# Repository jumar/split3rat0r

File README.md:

# d3vastat0r
My first 60 key ortholinear keyboard with top mounted components. 
This keyboard is inspired by the Plaid keyboard, but much simpler since I don't know enough to use all those components the Plaid uses.

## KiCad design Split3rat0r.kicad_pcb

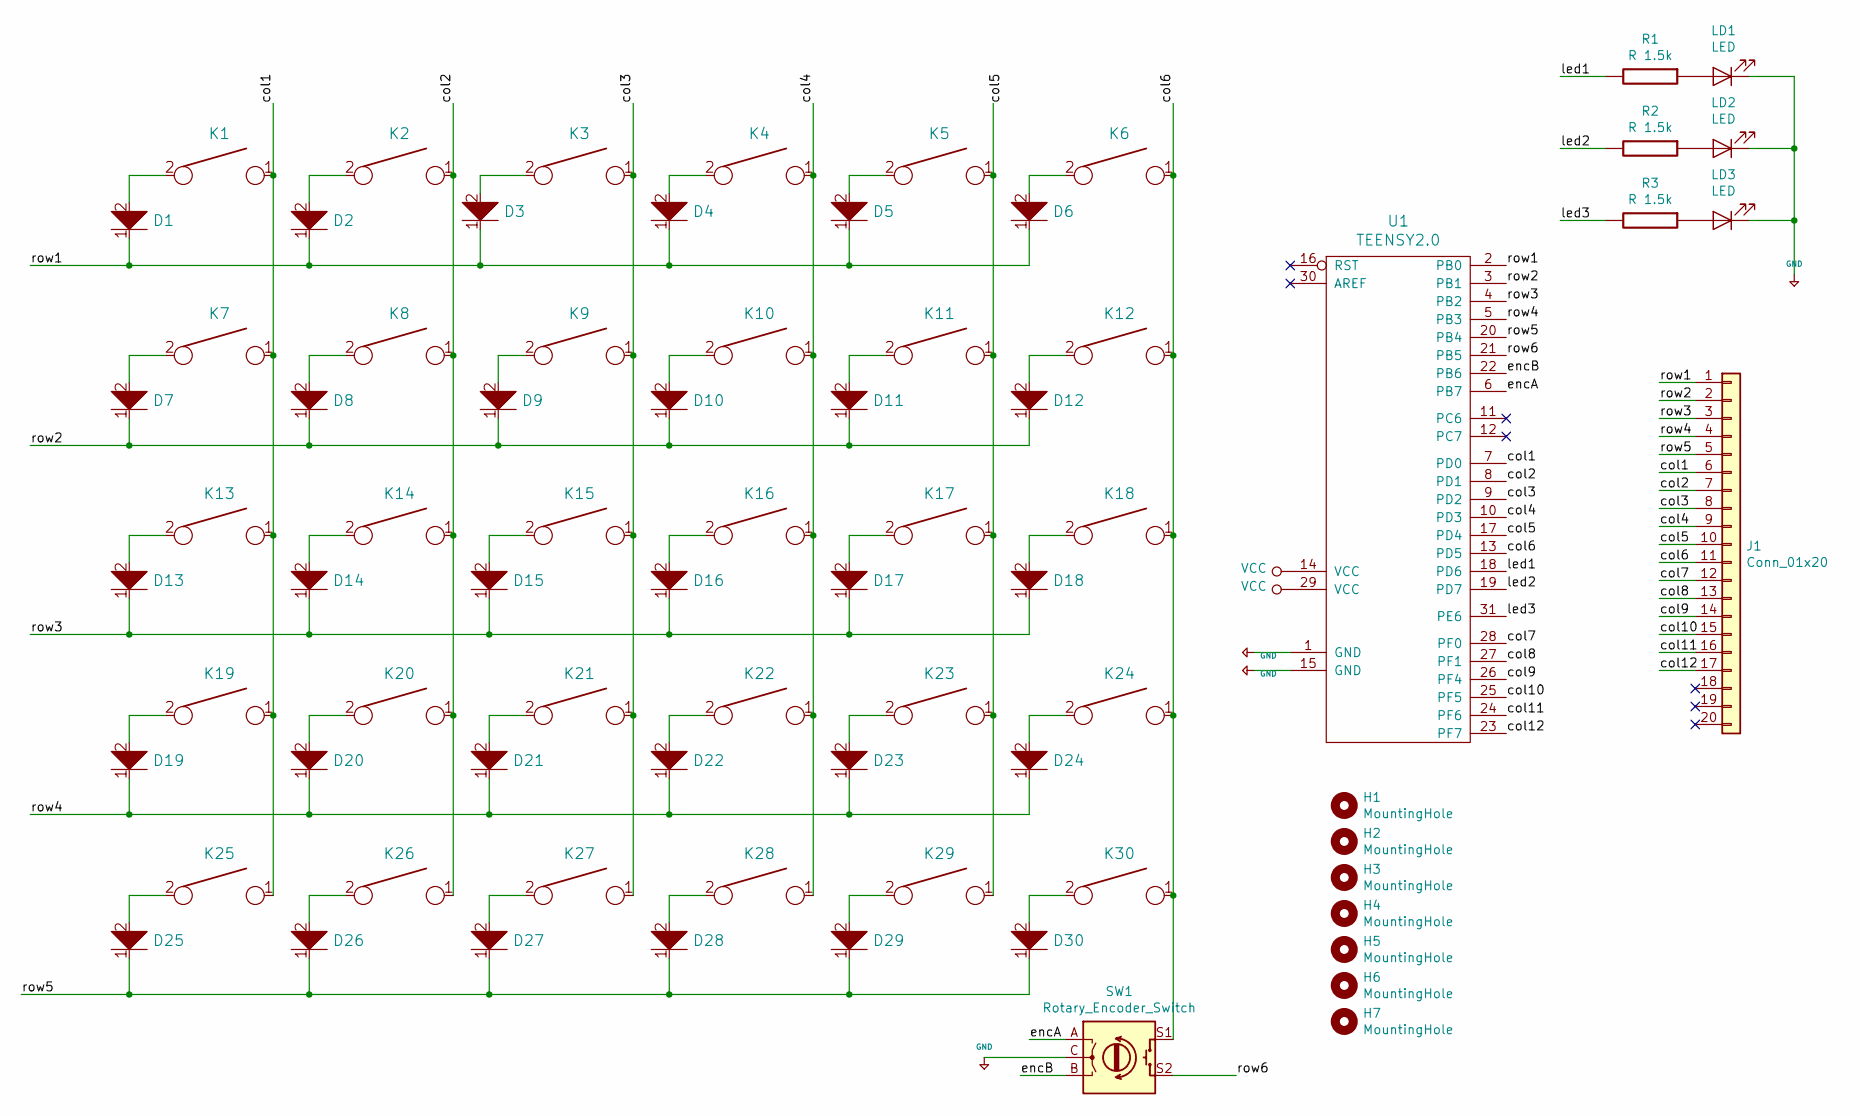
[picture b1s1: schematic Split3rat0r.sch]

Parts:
D1, D2, D3, D4, D5, D6, D7, D8, D9, D10, D11, D12, D13, D14, D15, D16, D17, D18, D19, D20, D21, D22, D23, D24, D25, D26, D27, D28, D29, D30: D; D_axial
H1, H2, H3, H4, H5, H6, H7: MountingHole; MountingHole_2.2mm_M2_Pad
J1: Conn_01x20; IDC-Header_2x10_P2.54mm_Horizontal
K1, K2, K3, K4, K5, K6, K7, K8, K9, K10, K11, K12, K13, K14, K15, K16, K17, K18, K19, K20, K21, K22, K23, K24, K25, K26, K27, K28, K29, K30: KEYSW; SW_Cherry_MX_1.00u_PCB
LD1, LD2, LD3: LED; LED_TH
R1, R2, R3: R 1.5k; R_Axial_DIN0204_L3.6mm_D1.6mm_P5.08mm_Horizontal
SW1: Rotary_Encoder_Switch; RotaryEncoder_Alps_EC11E-Switch_Vertical_H20mm
U1: TEENSY2.0; Teensy_20

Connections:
+5V: LD1.1 (K), LD2.1 (K), LD3.1 (K), SW1.C, U1.1 (GND), U1.15 (GND)
/col1: J1.6, K1.1, K7.1, K13.1, K19.1, K25.1, U1.7 (PD0)
/col2: J1.7, K2.1, K8.1, K14.1, K20.1, K26.1, U1.8 (PD1)
/col3: J1.8, K3.1, K9.1, K15.1, K21.1, K27.1, U1.9 (PD2)
/col4: J1.9, K4.1, K10.1, K16.1, K22.1, K28.1, U1.10 (PD3)
/col5: J1.10, U1.17 (PD4)
/col6: J1.11, K6.1, K12.1, K18.1, K24.1, K30.1, SW1.S1, U1.13 (PD5)
/col7: J1.12, U1.28 (PF0)
/col8: J1.13, U1.27 (PF1)
/col9: J1.14, U1.26 (PF4)
/col10: J1.15, U1.25 (PF5)
/col11: J1.16, U1.24 (PF6)
/col12: J1.17, U1.23 (PF7)
/encA: SW1.A, U1.6 (PB7)
/encB: SW1.B, U1.22 (PB6)
/led1: R1.2, U1.18 (PD6)
/led2: R2.2, U1.19 (PD7)
/led3: R3.2, U1.31 (PE6)
/row1: D1.1, D2.1, D3.1, D4.1, D5.1, D6.1, J1.1, U1.2 (PB0)
/row2: D7.1, D8.1, D9.1, D10.1, D11.1, D12.1, J1.2, U1.3 (PB1)
/row3: D13.1, D14.1, D15.1, D16.1, D17.1, D18.1, J1.3, U1.4 (PB2)
/row4: D19.1, D20.1, D21.1, D22.1, D23.1, D24.1, J1.4, U1.5 (PB3)
/row5: D25.1, D26.1, D27.1, D28.1, D29.1, D30.1, J1.5, U1.20 (PB4)
/row6: SW1.S2, U1.21 (PB5)
unnamed: D1.2, K1.2
unnamed: D2.2, K2.2
unnamed: D3.2, K3.2
unnamed: D4.2, K4.2
unnamed: D5.2, K5.2
unnamed: D6.2, K6.2
unnamed: D7.2, K7.2
unnamed: D8.2, K8.2
unnamed: D9.2, K9.2
unnamed: D10.2, K10.2
unnamed: D11.2, K11.2
unnamed: D12.2, K12.2
unnamed: D13.2, K13.2
unnamed: D14.2, K14.2
unnamed: D15.2, K15.2
unnamed: D16.2, K16.2
unnamed: D17.2, K17.2
unnamed: D18.2, K18.2
unnamed: D19.2, K19.2
unnamed: D20.2, K20.2
unnamed: D21.2, K21.2
unnamed: D22.2, K22.2
unnamed: D23.2, K23.2
unnamed: D24.2, K24.2
unnamed: D25.2, K25.2
unnamed: D26.2, K26.2
unnamed: D27.2, K27.2
unnamed: D28.2, K28.2
unnamed: D29.2, K29.2
unnamed: D30.2, K30.2
unnamed: K5.1, K11.1, K17.1, K23.1, K29.1
unnamed: LD1.2 (A), R1.1
unnamed: LD2.2 (A), R2.1
unnamed: LD3.2 (A), R3.1
VCC: U1.14 (VCC), U1.29 (VCC)

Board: 2 copper layers, 74 parts (0 on the bottom side), 59 nets, no tracks yet.

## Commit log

2019-05-07 Split3rat0r schenmatics
    First shot at a split ortho keyboard schematics with direct connection between hands
2019-05-07 Added LEDs beginning pcb layout
2019-05-08 Added rotary acoder switch + pcb layout progress
2019-05-13 mounting holes + edge cuts done
